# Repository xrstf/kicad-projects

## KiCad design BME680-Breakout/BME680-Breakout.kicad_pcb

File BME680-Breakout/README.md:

# Bosch BME680 Sensor Breakout Board

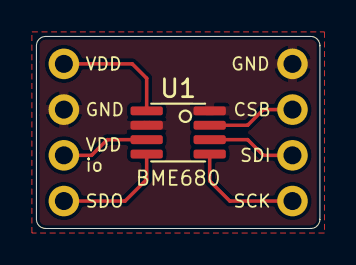
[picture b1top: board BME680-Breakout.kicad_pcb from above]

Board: 2 copper layers, 15.7 x 10.7 mm, 3 parts (0 on the bottom side), 7 nets.

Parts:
J1: LeftPins; PinHeader_1x04_P2.54mm_Vertical
J2: RightPins; PinHeader_1x04_P2.54mm_Vertical
U1: BME680; Bosch_LGA-8_3x3mm_P0.8mm_ClockwisePinNumbering_LargePads

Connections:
GNDREF: J1.2, J2.1, U1.1, U1.7
unnamed: J1.4, U1.5
unnamed: J2.2, U1.2
unnamed: J2.3, U1.3
unnamed: J2.4, U1.4
VCC: J1.3, U1.6
VDD: J1.1, U1.8

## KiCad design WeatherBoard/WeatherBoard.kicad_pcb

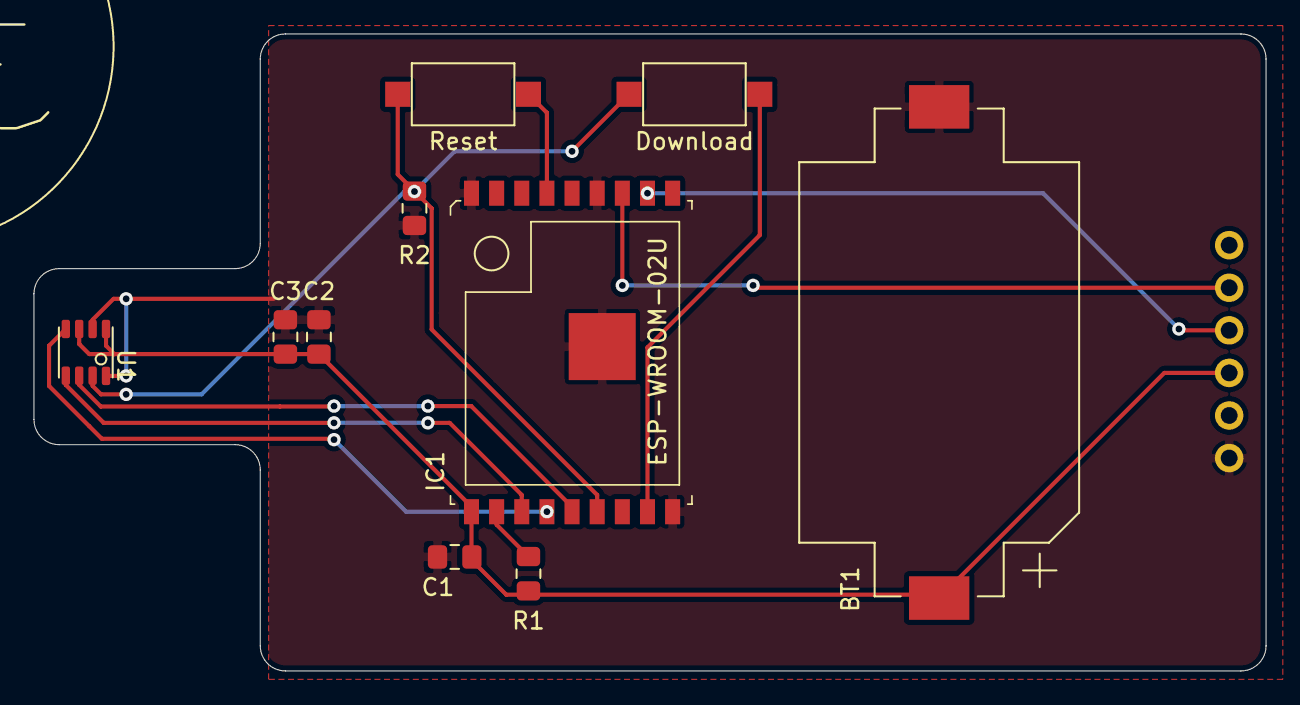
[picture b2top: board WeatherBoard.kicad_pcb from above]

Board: 2 copper layers, 73.5 x 38.0 mm, 11 parts (0 on the bottom side), 11 nets.

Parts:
BT1: CR2032; BatteryHolder_Keystone_1060_1x2032
C1, C2, C3: 10uF; C_0805_2012Metric_Pad1.15x1.40mm_HandSolder
Download: DownloadBtn; SW_SPST_CK_RS282G05A3
IC1: ESP-WROOM-02U__4MB_; ESP-WROOM-02U
J1: UART; PinHeader_1x06_P2.54mm_Vertical
R1: 10K PullUp; R_0805_2012Metric_Pad1.15x1.40mm_HandSolder
R2: 10K PullDown; R_0805_2012Metric_Pad1.15x1.40mm_HandSolder
Reset: ResetBtn; SW_SPST_CK_RS282G05A3
U1: BME680; Bosch_LGA-8_3x3mm_P0.8mm_ClockwisePinNumbering

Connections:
+3V3: BT1.1, C1.2, C2.1, C3.2, IC1.1, J1.4, R1.1, U1.6, U1.8
GNDREF: BT1.2, C1.1, C2.2, C3.1, IC1.9, IC1.13, IC1.18, IC1.19, J1.6, R2.1, U1.1, U1.7
unnamed: IC1.2, R1.2
unnamed: IC1.3, U1.4
unnamed: IC1.4, U1.5
unnamed: IC1.5, U1.3
unnamed: Download.2, IC1.6, R2.2, Reset.1, U1.2
unnamed: Download.1, IC1.8
unnamed: IC1.11, J1.3
unnamed: IC1.12, J1.2
unnamed: IC1.15, Reset.2

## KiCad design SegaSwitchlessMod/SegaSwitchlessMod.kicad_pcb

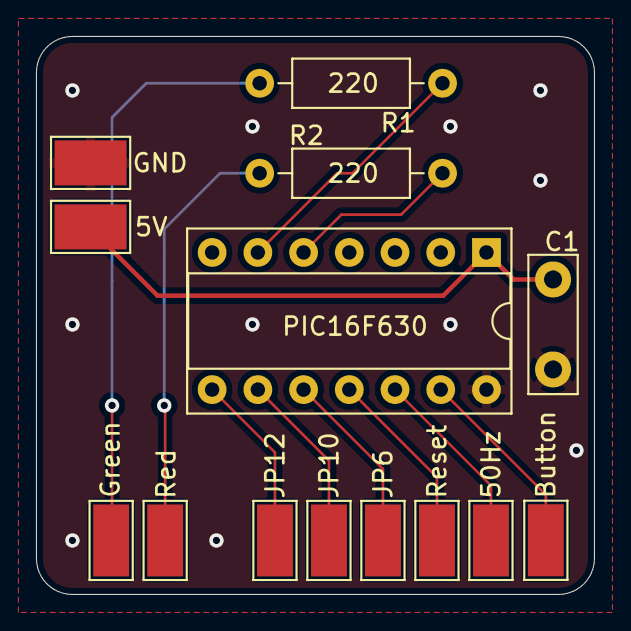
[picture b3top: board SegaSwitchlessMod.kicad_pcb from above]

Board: 2 copper layers, 31.0 x 31.0 mm, 14 parts (0 on the bottom side), 12 nets.

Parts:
5V: 5V; WireSolderPad_2.5x4.0mm
50Hz: 50; WireSolderPad_2.0x4.0mm
Button: BUTTON; WireSolderPad_2.0x4.0mm
C1: 100nF; C_Disc_D7.5mm_W2.5mm_P5.00mm
GND: Ground; WireSolderPad_2.5x4.0mm
Green: Green; WireSolderPad_2.0x4.0mm
JP6: JP6; WireSolderPad_2.0x4.0mm
JP10: JP10; WireSolderPad_2.0x4.0mm
JP12: JP12; WireSolderPad_2.0x4.0mm
R1, R2: 220; R_Axial_DIN0207_L6.3mm_D2.5mm_P10.16mm_Horizontal
Red: Red; WireSolderPad_2.0x4.0mm
Reset: RST; WireSolderPad_2.0x4.0mm
U4: PIC16F630-IP; DIP-14_W7.62mm_Socket

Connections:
+5V: 5V.1, C1.2, U4.1
GND: C1.1, GND.1, U4.14
unnamed: Green.1, R1.1
unnamed: R1.2, U4.6
unnamed: R2.1, Red.1
unnamed: R2.2, U4.5
unnamed: Button.1, U4.13
unnamed: 50Hz.1, U4.12
unnamed: Reset.1, U4.11
unnamed: JP12.1, U4.8
unnamed: JP10.1, U4.9
unnamed: JP6.1, U4.10

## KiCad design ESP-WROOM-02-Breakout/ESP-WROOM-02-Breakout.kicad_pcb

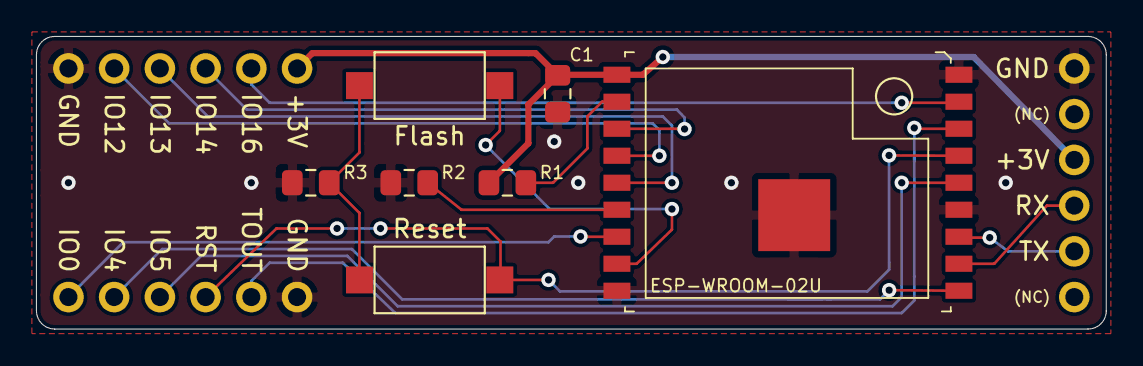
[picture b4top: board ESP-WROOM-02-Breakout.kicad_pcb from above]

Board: 2 copper layers, 59.4 x 16.3 mm, 10 parts (1 on the bottom side), 17 nets.

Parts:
C1: 10uF; C_0805_2012Metric_Pad1.15x1.40mm_HandSolder
Flash: DownloadModeBtn; SW_SPST_CK_RS282G05A3
IC1: ESP-WROOM-02U__4MB_; ESP-WROOM-02U
J1: Left Pins; PinHeader_1x06_P2.54mm_Vertical
J2: Right Pins; PinHeader_1x06_P2.54mm_Vertical
J3: UART; PinHeader_1x06_P2.54mm_Vertical
R1, R2, R3: 10K; R_0805_2012Metric_Pad1.15x1.40mm_HandSolder
Reset: ResetBtn; SW_SPST_CK_RS282G05A3

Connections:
+3V3: C1.2, IC1.1, J1.6, J3.4, R1.1
GNDREF: C1.1, IC1.9, IC1.13, IC1.18, IC1.19, J1.1, J2.1, J3.6, R2.2, R3.1
unnamed: IC1.2, R1.2
unnamed: IC1.3, J1.4
unnamed: IC1.4, J1.2
unnamed: IC1.5, J1.3
unnamed: IC1.6, R2.1
unnamed: IC1.7, J2.6
unnamed: Flash.1, IC1.8
unnamed: IC1.10, J2.5
unnamed: IC1.11, J3.3
unnamed: IC1.12, J3.2
unnamed: IC1.14, J2.4
unnamed: IC1.15, J2.3, Reset.2
unnamed: IC1.16, J2.2
unnamed: IC1.17, J1.5
unnamed: Flash.2, R3.2, Reset.1

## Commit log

2020-07-08 add SegaSwitchlessMod
2020-07-09 add ESP-WROOM-02U-Breakout
2020-07-12 improve esp footprint, small fixes
2020-07-12 move all components to one side, try to keep it hand-solder friendly
2020-07-18 redesign ESP breakout board to be longer and thinner with buttons
2020-07-18 use reset pin instead of cutting power, tidy up a bit
2020-07-18 add voltage/current/wifi info on silkscreen
2020-07-19 add BME680 breakout board
2020-07-19 re-layout sega mod to fit Mega Drive II better
2020-07-19 add screenshot
2020-07-19 add another readme
2020-07-20 add Global Parts library
2020-07-20 first draft for WeatherBoard
2020-07-24 use a BME680 footprint with much larger solder pads for greatier happiness

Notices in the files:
BME680-Breakout/BME680-Breakout.kicad_pcb:
CC BY-SA 4.0
ESP-WROOM-02-Breakout/ESP-WROOM-02-Breakout.kicad_pcb:
© xrstf.de (CC BY-SA 4.0)
